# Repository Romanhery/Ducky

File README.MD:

# Ducky

This is my b2b Saas + Hardware. Assistant that Actually helps you! + Some features.

## Features

- You can Talk to it 
- It Looks cool and cute on your desk
- It allows you to think outloud and actually proccess your ideas.
- Idea mode to track ideas
- Todo mode to track your TODO's

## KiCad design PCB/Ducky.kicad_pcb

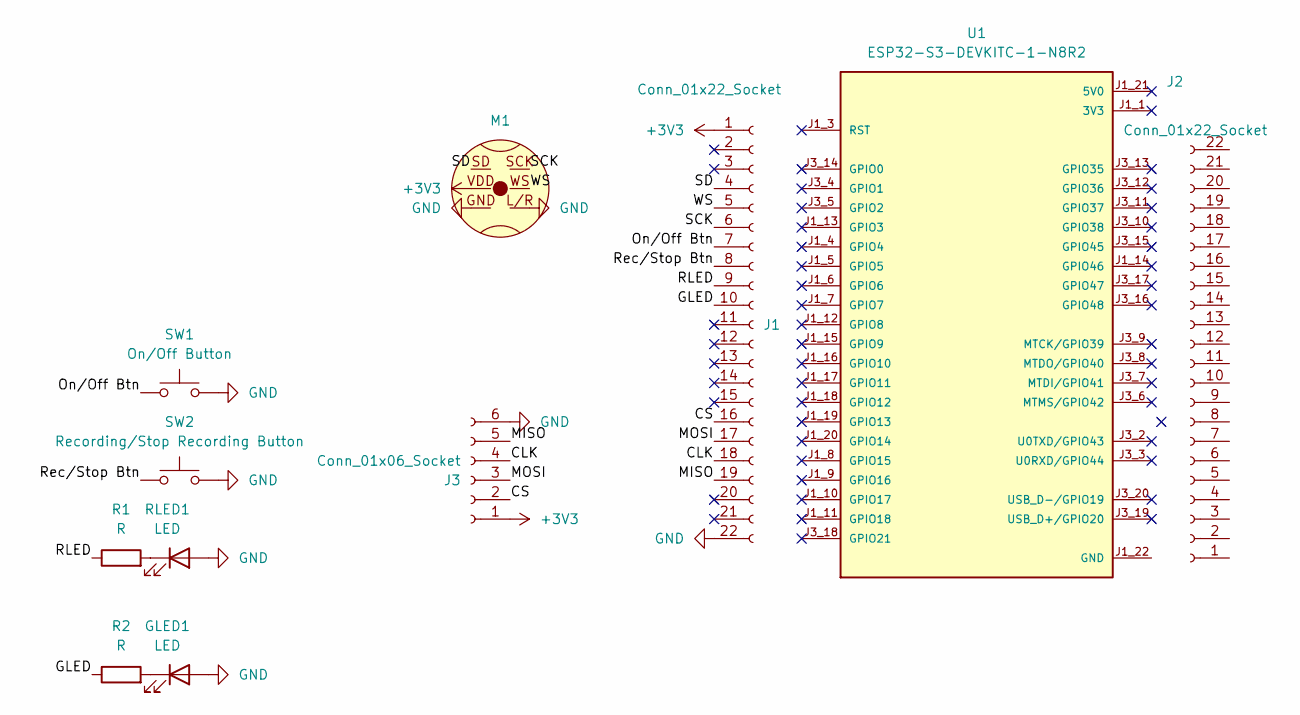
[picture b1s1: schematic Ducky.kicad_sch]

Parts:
GLED1: LED; LED_D5.0mm
J1, J2: Conn_01x22_Socket; PinSocket_1x22_P2.54mm_Vertical
J3: Conn_01x06_Socket; PinSocket_1x06_P2.54mm_Vertical
M1: INMP441_Module_D14_v2
R1, R2: R; R_Axial_DIN0207_L6.3mm_D2.5mm_P7.62mm_Horizontal
RLED1: LED; LED_D5.0mm
SW1: On/Off Button; SW_PUSH_6mm_H7.3mm
SW2: Recording/Stop Recording Button; SW_PUSH_6mm_H7.3mm
U1: ESP32-S3-DEVKITC-1-N8R2; XCVR_ESP32-S3-DEVKITC-1-N8R2; PARTREV V1

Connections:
+3V3: J1.1, J3.1, M1.VDD
/CLK: J1.18, J3.4
/CS: J1.16, J3.2
/GLED: J1.10, R2.1
/MISO: J1.19, J3.5
/MOSI: J1.17, J3.3
/On/Off Btn: J1.7, SW1.1
/RLED: J1.9, R1.1
/Rec/Stop Btn: J1.8, SW2.1
/SCK: J1.6, M1.SCK
/SD: J1.4, M1.SD
/WS: J1.5, M1.WS
GND: GLED1.2 (A), J1.22, J3.6, M1.GND, M1.L/R, RLED1.2 (A), SW1.2, SW2.2
unnamed: GLED1.1 (K), R2.2
unnamed: R1.2, RLED1.1 (K)
unnamed: U1.J1_1 (3V3), U1.J1_2 (3V3)
unnamed: U1.J1_22 (GND), U1.J3_1 (GND), U1.J3_21 (GND), U1.J3_22 (GND)

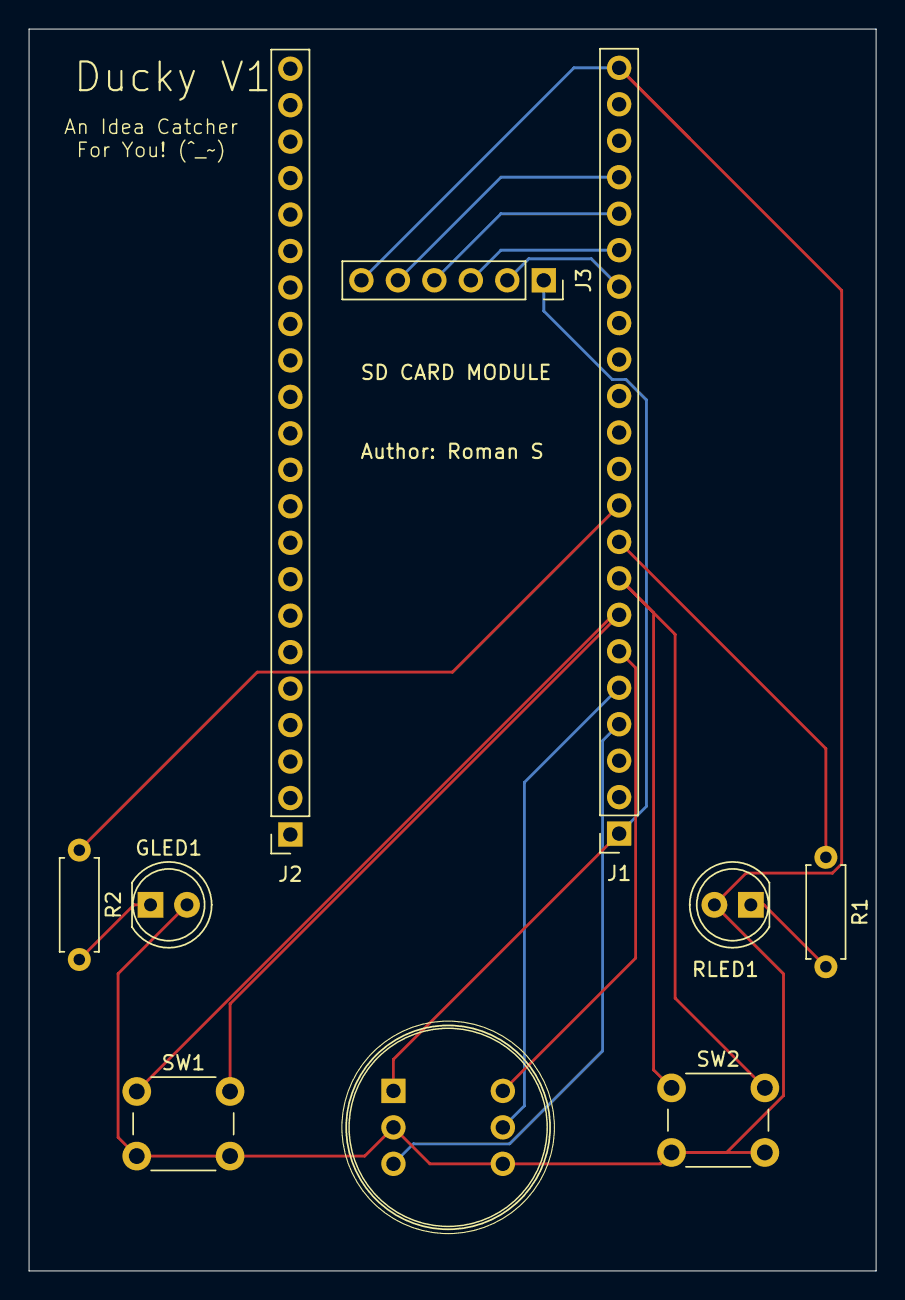
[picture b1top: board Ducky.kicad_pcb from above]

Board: 2 copper layers, 59.0 x 86.5 mm, 10 parts (0 on the bottom side), 15 nets.
